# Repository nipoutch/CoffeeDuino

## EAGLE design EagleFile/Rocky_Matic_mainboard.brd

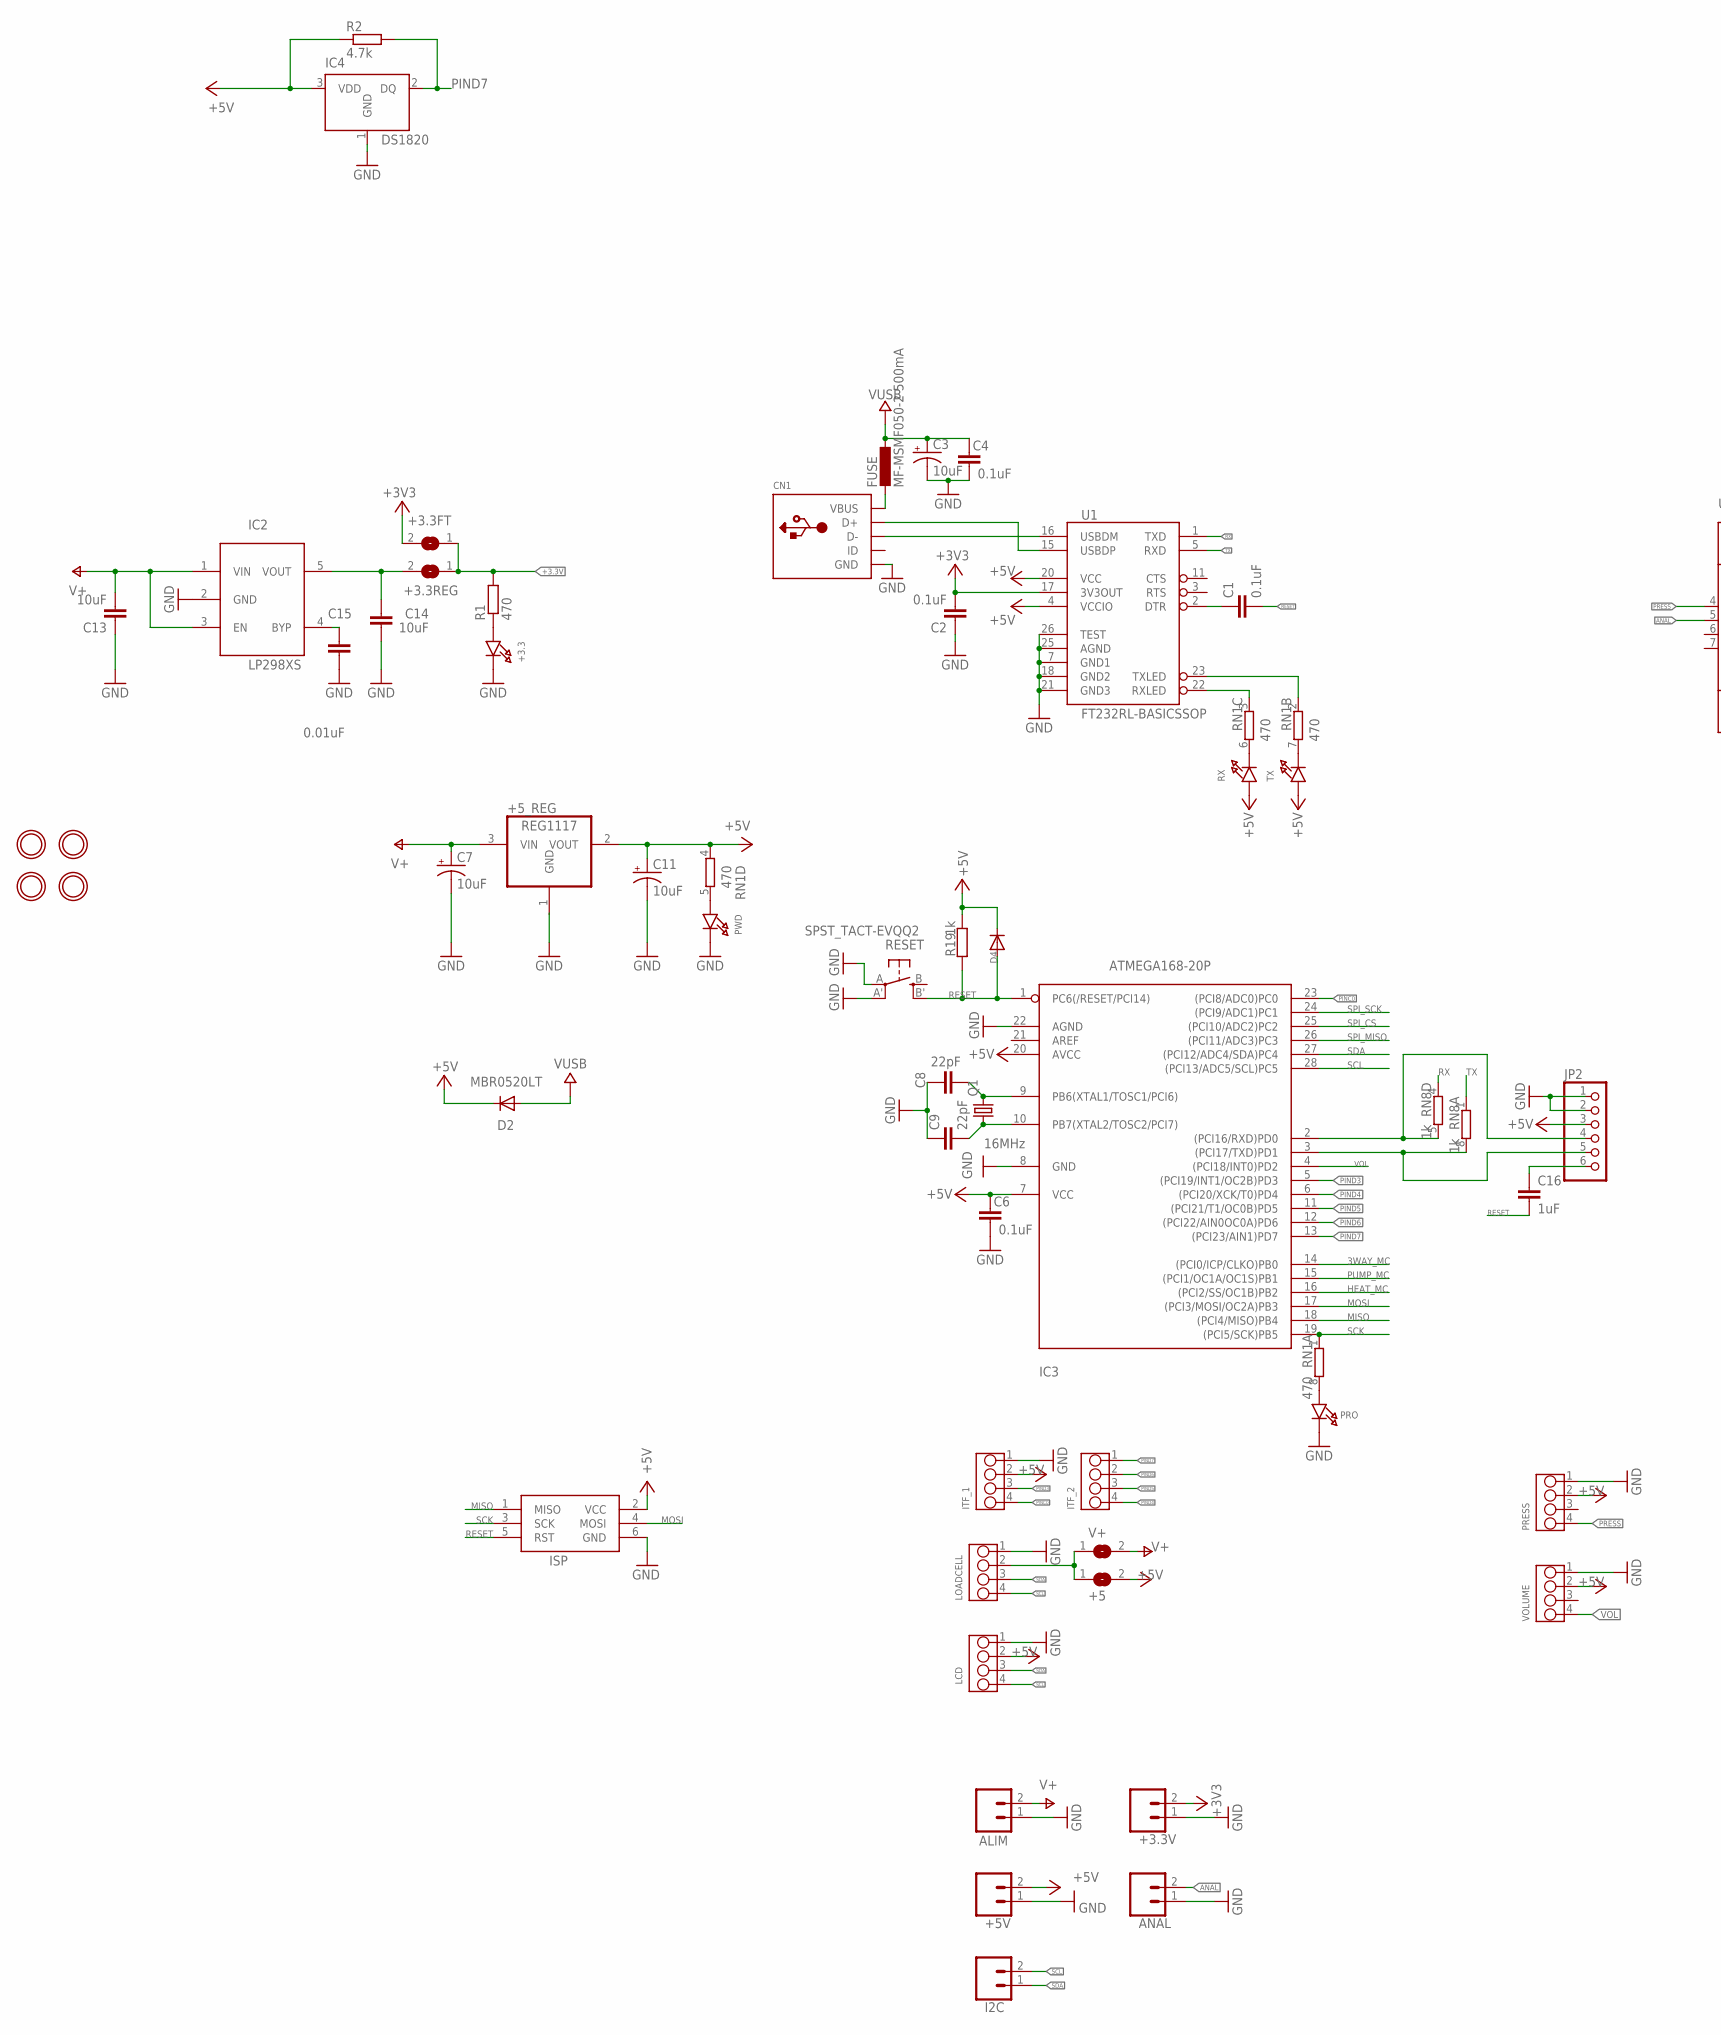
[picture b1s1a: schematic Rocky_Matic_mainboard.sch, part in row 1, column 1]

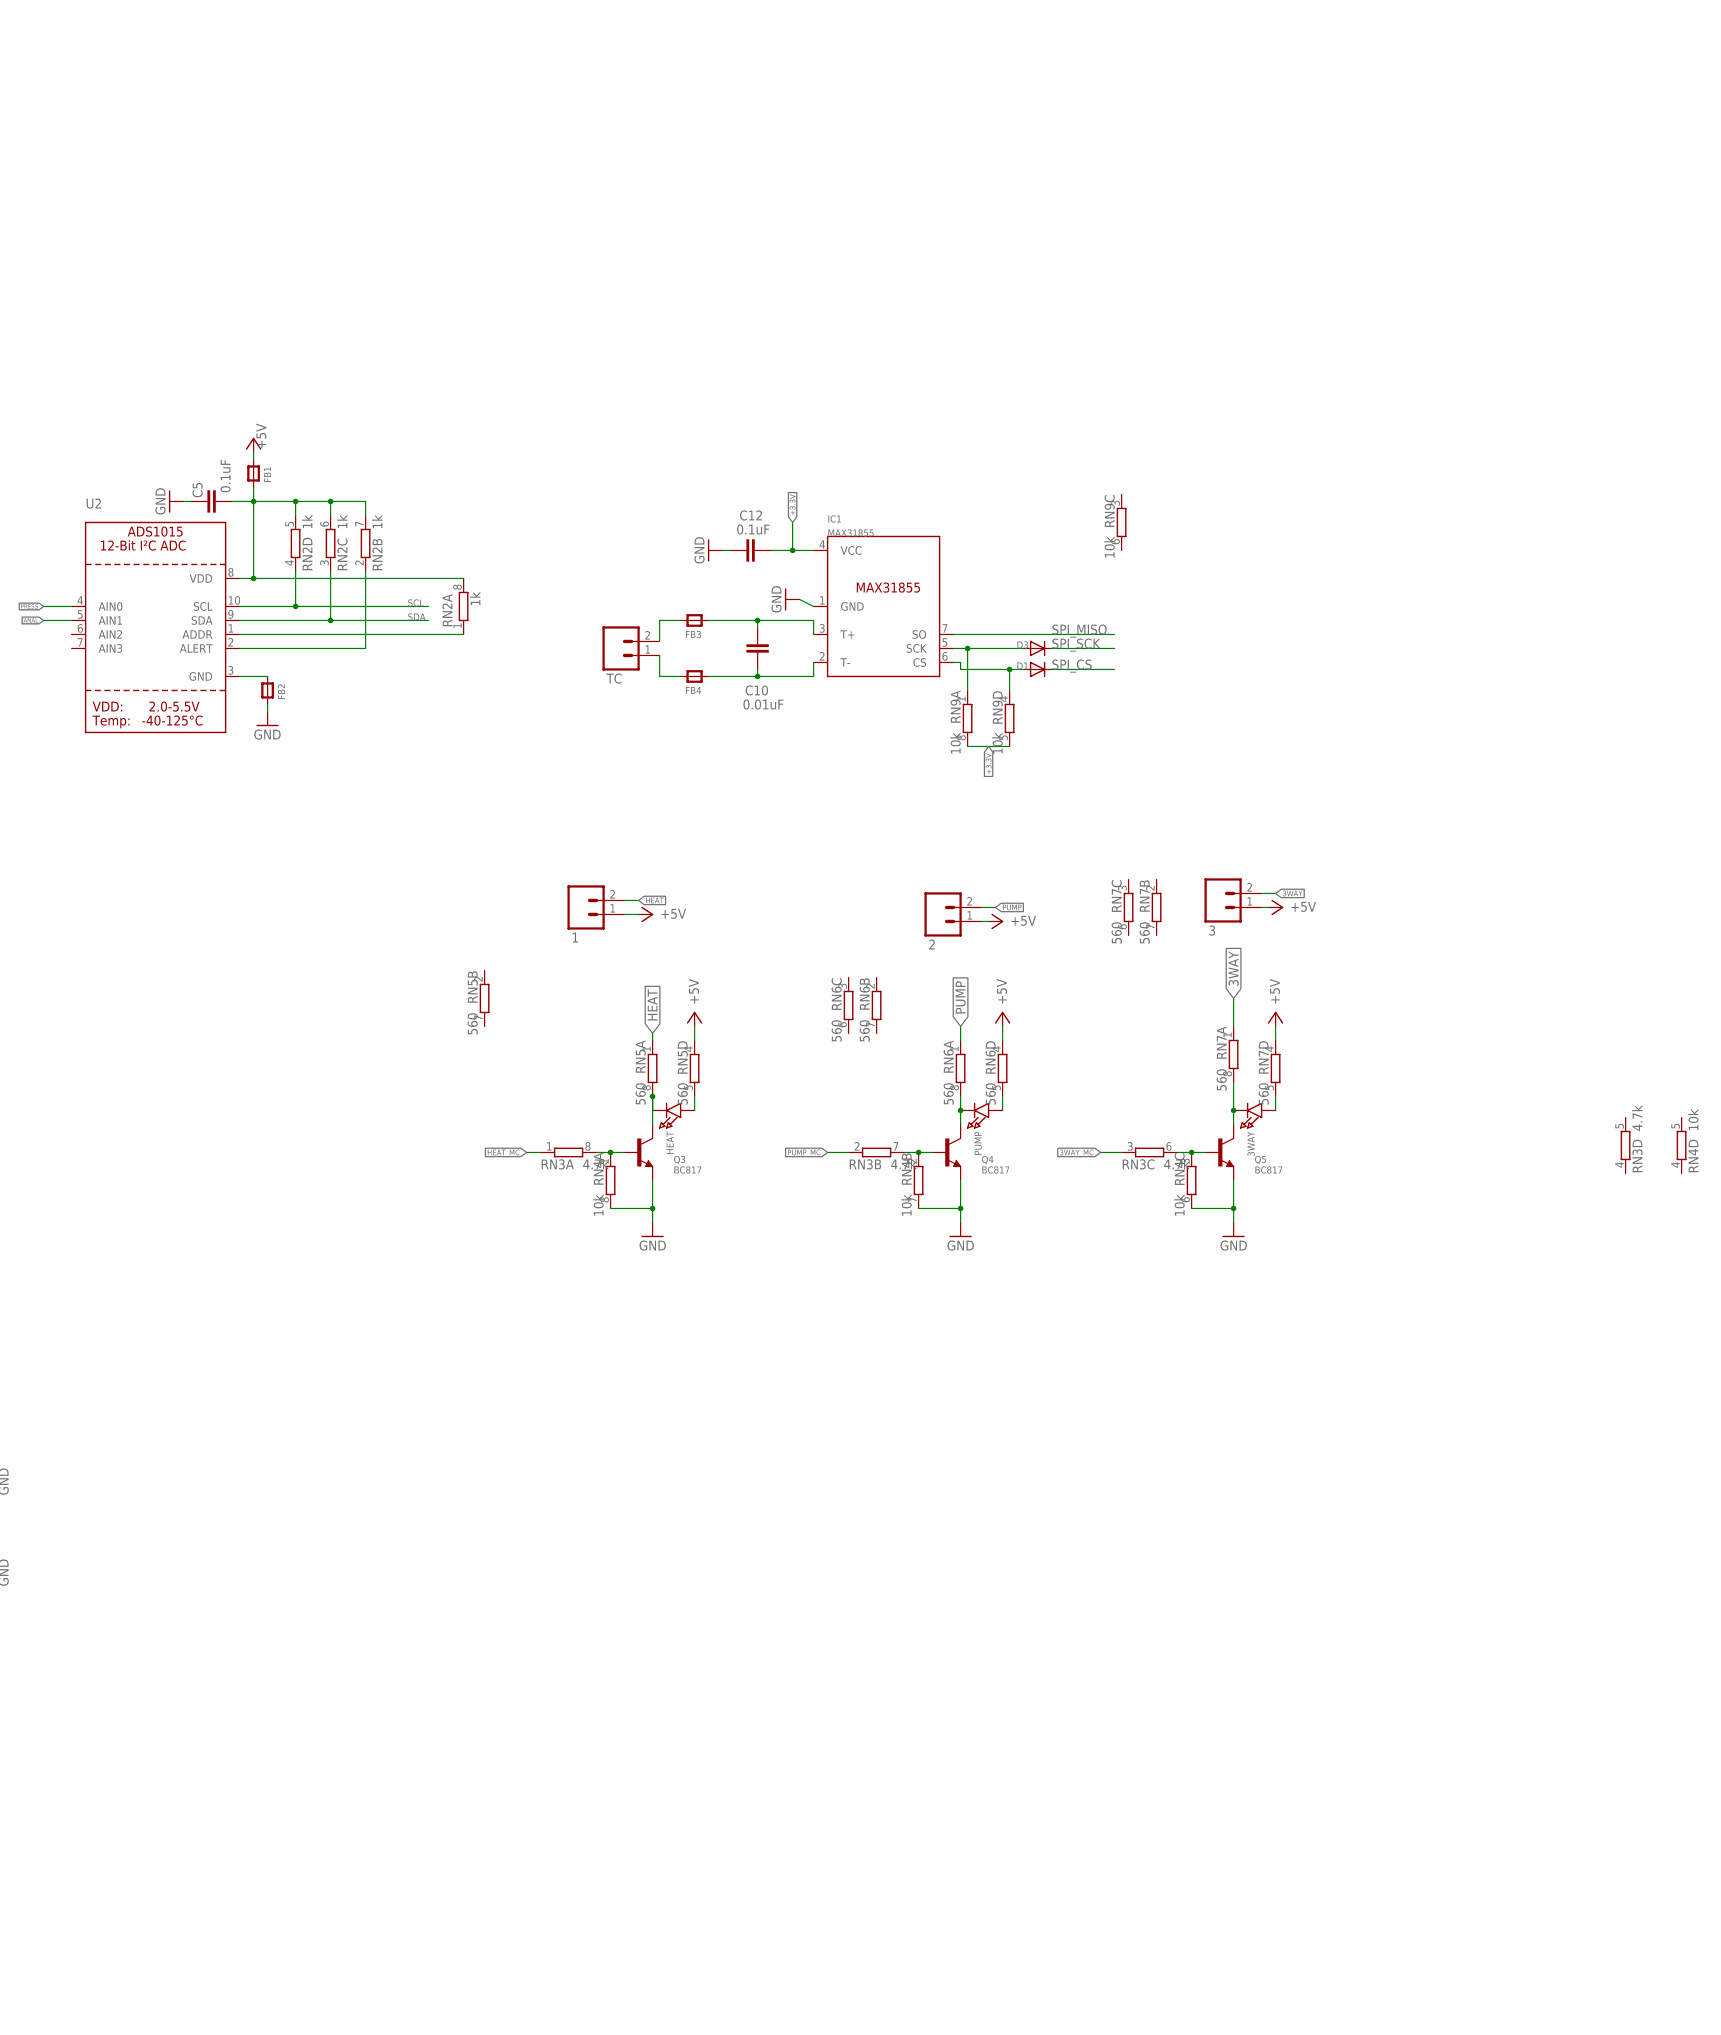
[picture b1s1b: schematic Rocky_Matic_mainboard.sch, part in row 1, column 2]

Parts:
1, 2, 3: M023.5MM; SCREWTERMINAL-3.5MM-2
3WAY: LED0805; CHIPLED_0805
+3.3: LED0805; CHIPLED_0805
+3.3FT, +3.3REG, +5: SJ
+3.3V, +5V: M023.5MM; SCREWTERMINAL-3.5MM-2
+5_REG: REG1117; SOT223
ALIM: M023.5MM; SCREWTERMINAL-3.5MM-2
ANAL: M023.5MM; SCREWTERMINAL-3.5MM-2
C1, C2, C4, C5, C6, C12: 0.1uF; C0805
C3, C7, C11: 10uF; EIA3216
C8, C9: 22pF; C0805
C10, C15: 0.01uF; C0805
C13, C14: 10uF; C0805
C16: 1uF; C0805
CN1: USBMINIB; USB-MINIB
D1, D3, D4: DIODESOD-323F; SOD-323F
D2: MBR0520LT; SOD123
FB1, FB2, FB3, FB4: FERRITE_0805; _0805
FUSE: MF-MSMF050-2 500mA; L1812
HEAT: LED0805; CHIPLED_0805
I2C: M023.5MM; SCREWTERMINAL-3.5MM-2
IC1: MAX31855; SOIC8
IC2: LP298XS; SOT23-5L
IC3: ATMEGA168-20P; DIL28-3
IC4: DS1820; TO-92
ISP: AVRISP-6; AVRISP
ITF_1, ITF_2: GROVE-4P-2.0-3470140P1; 4P-2.0-90D
JP2: PINHD-1X6B; 1X06-BIG
LCD: GROVE-4P-2.0-3470140P1; 4P-2.0-90D
LOADCELL: GROVE-4P-2.0-3470140P1; 4P-2.0-90D
PRESS: GROVE-4P-2.0-3470140P1; 4P-2.0-90D
PRO: LED0805; CHIPLED_0805
PUMP: LED0805; CHIPLED_0805
PWD: LED0805; CHIPLED_0805
Q1: 16MHz; CTS406
Q3, Q4, Q5: BC817; SOT23-R
R1: 470; R0805
R2: 4.7k; R0805
R19: 1k; M0805
RESET: SPST_TACT-EVQQ2; EVQ-Q2
RN1: 470; CAY16
RN2: 1k; CAT16
RN3: 4.7k; CAT16
RN4, RN9: 10k; CAT16
RN5, RN6, RN7: 560; CAT16
RN8: 1k; CAY16
RX: LED0805; CHIPLED_0805
TC: M023.5MM; SCREWTERMINAL-3.5MM-2
TX: LED0805; CHIPLED_0805
U1: FT232RL-BASICSSOP; SSOP28DB
U2: ADC_ADS1015; MSOP10
U$1, U$2, U$3, U$4: MOUNTINGHOLE3.0THIN; MOUNTINGHOLE_3.0_PLATEDTHIN
V+: SJ
VOLUME: GROVE-4P-2.0-3470140P1; 4P-2.0-90D

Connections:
3WAY: 3.2, RN7.1
3WAY_MC: IC3.14 ((PCI0/ICP/CLKO)PB0), RN3.3 (1)
+3.3V: +3.3FT.1, +3.3REG.1, C12.2, IC1.4 (VCC), R1.2, RN9.5 (2), RN9.8 (2)
+3V3: +3.3FT.2, +3.3V.2, C2.2, U1.17 (3V3OUT)
+5V: 1.1, 2.1, 3.1, +5.2, +5V.2, +5_REG.2 (VOUT), C6.2, C11.A (+), D2.C, D4.C, FB1.1, IC3.7 (VCC), IC3.20 (AVCC), IC4.3 (VDD), ISP.2 (VCC), ITF_1.2, JP2.3, LCD.2, PRESS.2, R2.1, R19.2, RN1.4 (1), RN5.4 (1), RN6.4 (1), RN7.4 (1), RX.A, TX.A, U1.4 (VCCIO), U1.20 (VCC), VOLUME.2
ANAL: ANAL.2, U2.5 (AIN1)
GND: +3.3.C, +3.3V.1, +5V.1, +5_REG.1 (GND), ALIM.1, ANAL.1, C2.1, C3.C (-), C4.1, C5.2, C6.1, C7.C (-), C8.1, C9.1, C11.C (-), C12.1, C13.1, C14.1, C15.1, CN1.GND, FB2.2, IC1.1 (GND), IC2.2 (GND), IC3.8 (GND), IC3.22 (AGND), IC4.1 (GND), ISP.6 (GND), ITF_1.1, JP2.1, JP2.2, LCD.1, LOADCELL.1, PRESS.1, PRO.C, PWD.C, Q3.2 (E), Q4.2 (E), Q5.2 (E), RESET.A, RESET.A' (P1), RN4.6 (2), RN4.7 (2), RN4.8 (2), U1.7 (GND1), U1.18 (GND2), U1.21 (GND3), U1.25 (AGND), U1.26 (TEST), VOLUME.1
HEAT: 1.2, RN5.1
HEAT_MC: IC3.16 ((PCI2/SS/OC1B)PB2), RN3.1
MISO: IC3.18 ((PCI4/MISO)PB4), ISP.1 (MISO)
MOSI: IC3.17 ((PCI3/MOSI/OC2A)PB3), ISP.4 (MOSI)
unnamed: Q3.1 (B), RN3.8 (2), RN4.1
unnamed: C8.2, IC3.9 (PB6(XTAL1/TOSC1/PCI6)), Q1.3 (2)
unnamed: HEAT.C, Q3.3 (C), RN5.8 (2)
unnamed: C9.2, IC3.10 (PB7(XTAL2/TOSC2/PCI7)), Q1.1
unnamed: HEAT.A, RN5.5 (2)
unnamed: CN1.VBUS, FUSE.2
unnamed: Q4.1 (B), RN3.7 (2), RN4.2 (1)
unnamed: PUMP.C, Q4.3 (C), RN6.8 (2)
unnamed: PUMP.A, RN6.5 (2)
unnamed: RN1.7 (2), TX.C
unnamed: Q5.1 (B), RN3.6 (2), RN4.3 (1)
unnamed: PWD.A, RN1.5 (2)
unnamed: 3WAY.C, Q5.3 (C), RN7.8 (2)
unnamed: 3WAY.A, RN7.5 (2)
unnamed: RN1.6 (2), RX.C
unnamed: FB2.1, U2.3 (GND)
unnamed: RN1.3 (1), U1.22 (RXLED)
unnamed: RN1.2 (1), U1.23 (TXLED)
unnamed: CN1.D+, U1.15 (USBDP)
unnamed: C1.1, U1.2 (DTR)
unnamed: CN1.D-, U1.16 (USBDM)
unnamed: RN2.1, U2.1 (ADDR)
unnamed: IC3.2 ((PCI16/RXD)PD0), JP2.4, RN8.5 (2)
unnamed: IC3.3 ((PCI17/TXD)PD1), JP2.5, RN8.8 (2)
unnamed: RN2.2 (1), U2.2 (ALERT)
unnamed: PRO.A, RN1.8 (2)
unnamed: C10.1, FB3.1, IC1.3 (T+)
unnamed: C10.2, FB4.1, IC1.2 (T-)
unnamed: C5.1, FB1.2, RN2.5 (2), RN2.6 (2), RN2.7 (2), RN2.8 (2), U2.8 (VDD)
unnamed: FB3.2, TC.2
unnamed: FB4.2, TC.1
unnamed: D3.A, IC1.5 (SCK), RN9.1
unnamed: D1.A, IC1.6 (CS), RN9.4 (1)
unnamed: +5.1, LOADCELL.2, V+.1
unnamed: +3.3.A, R1.1
unnamed: +3.3REG.2, C14.2, IC2.5 (VOUT)
unnamed: C15.2, IC2.4 (BYP)
unnamed: C16.1, JP2.6
PINC0: IC3.23 ((PCI8/ADC0)PC0), ITF_1.4
PIND3: IC3.5 ((PCI19/INT1/OC2B)PD3), ITF_1.3
PIND4: IC3.6 ((PCI20/XCK/T0)PD4), ITF_2.4
PIND5: IC3.11 ((PCI21/T1/OC0B)PD5), ITF_2.3
PIND6: IC3.12 ((PCI22/AIN0OC0A)PD6), ITF_2.2
PIND7: IC3.13 ((PCI23/AIN1)PD7), IC4.2 (DQ), ITF_2.1, R2.2
PRESS: PRESS.4, U2.4 (AIN0)
PUMP: 2.2, RN6.1
PUMP_MC: IC3.15 ((PCI1/OC1A/OC1S)PB1), RN3.2 (1)
RESET: C1.2, C16.2, D4.A, IC3.1 (PC6(/RESET/PCI14)), ISP.5 (RST), R19.1, RESET.B' (S1)
RX: RN8.4 (1), U1.1 (TXD)
SCK: IC3.19 ((PCI5/SCK)PB5), ISP.3 (SCK), RN1.1
SCL: I2C.2, IC3.28 ((PCI13/ADC5/SCL)PC5), LCD.4, LOADCELL.4, RN2.4 (1), U2.10 (SCL)
SDA: I2C.1, IC3.27 ((PCI12/ADC4/SDA)PC4), LCD.3, LOADCELL.3, RN2.3 (1), U2.9 (SDA)
SPI_CS: D1.C, IC3.25 ((PCI10/ADC2)PC2)
SPI_MISO: IC1.7 (SO), IC3.26 ((PCI11/ADC3)PC3)
SPI_SCK: D3.C, IC3.24 ((PCI9/ADC1)PC1)
TX: RN8.1, U1.5 (RXD)
V+: +5_REG.3 (VIN), ALIM.2, C7.A (+), C13.2, IC2.1 (VIN), IC2.3 (EN), V+.2
VOL: IC3.4 ((PCI18/INT0)PD2), VOLUME.4
VUSB: C3.A (+), C4.2, D2.A, FUSE.1

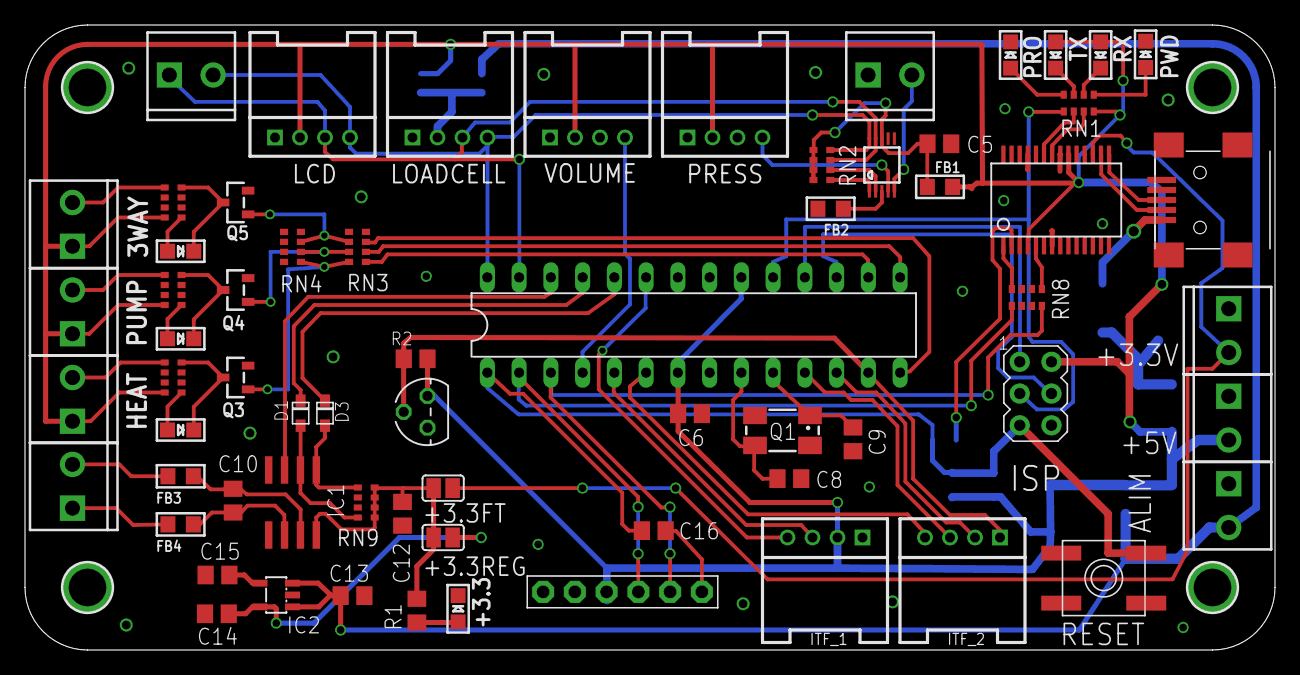
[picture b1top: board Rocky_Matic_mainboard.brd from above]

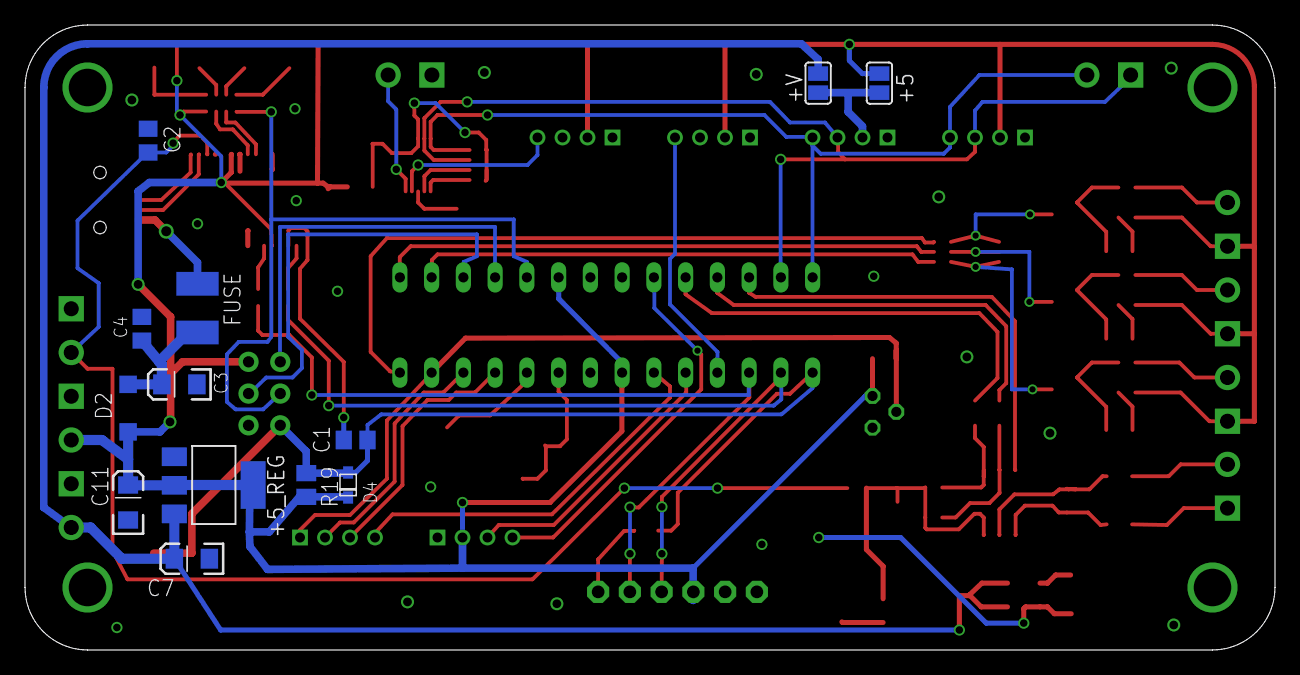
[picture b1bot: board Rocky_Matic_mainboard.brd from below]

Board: 4 copper layers, 100.0 x 50.0 mm, 83 parts (13 on the bottom side), 70 nets.

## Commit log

2014-07-12 Code arduino pour la carte CoffeeDuino
2014-07-15 test
2014-07-15 nettoyage du code
2014-07-16 optimisation de la partie MANUELLE
2014-07-22 Décimation et Moyenne Mobile
    ajout de décimation et moyenne mobile pour la partie ADC
2014-07-22 Arrondi
2014-07-26 Update
    Balance dans tout les modes
2014-07-28 With Lib for ads1115
2014-07-28 With EagleFile
2014-07-29 Updayte
2014-09-04 hx711 version

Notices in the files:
parts and their libraries:
SparkFun-Capacitors: Licensing: Creative Commons ShareAlike 4.0 International - https://creativecommons.org/licenses/by-sa/4.0
microbuilder: This work is placed in the public domain, and may be freely used for commercial and non-commercial work with the following conditions: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
